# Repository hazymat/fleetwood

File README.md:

# fleetwood
Home Automation Room Controller

*** NOTE: Support for this project is not possible, however collaborators are warmly encouraged to contact me! ***

Project consists of:
- Arduino Sketch intended for Arduino Mega 2560
- Eagle files for 4 PC boards

1/ Sketch and Eagle schematics and board layouts are shared for information only.
2/ This project does not yet include an official BOM.

   Copyright 2015 Mat Smith

   Licensed under the Apache License, Version 2.0 (the "License");
   you may not use this file except in compliance with the License.
   You may obtain a copy of the License at

       http://www.apache.org/licenses/LICENSE-2.0

   Unless required by applicable law or agreed to in writing, software
   distributed under the License is distributed on an "AS IS" BASIS,
   WITHOUT WARRANTIES OR CONDITIONS OF ANY KIND, either express or implied.
   See the License for the specific language governing permissions and
   limitations under the License.

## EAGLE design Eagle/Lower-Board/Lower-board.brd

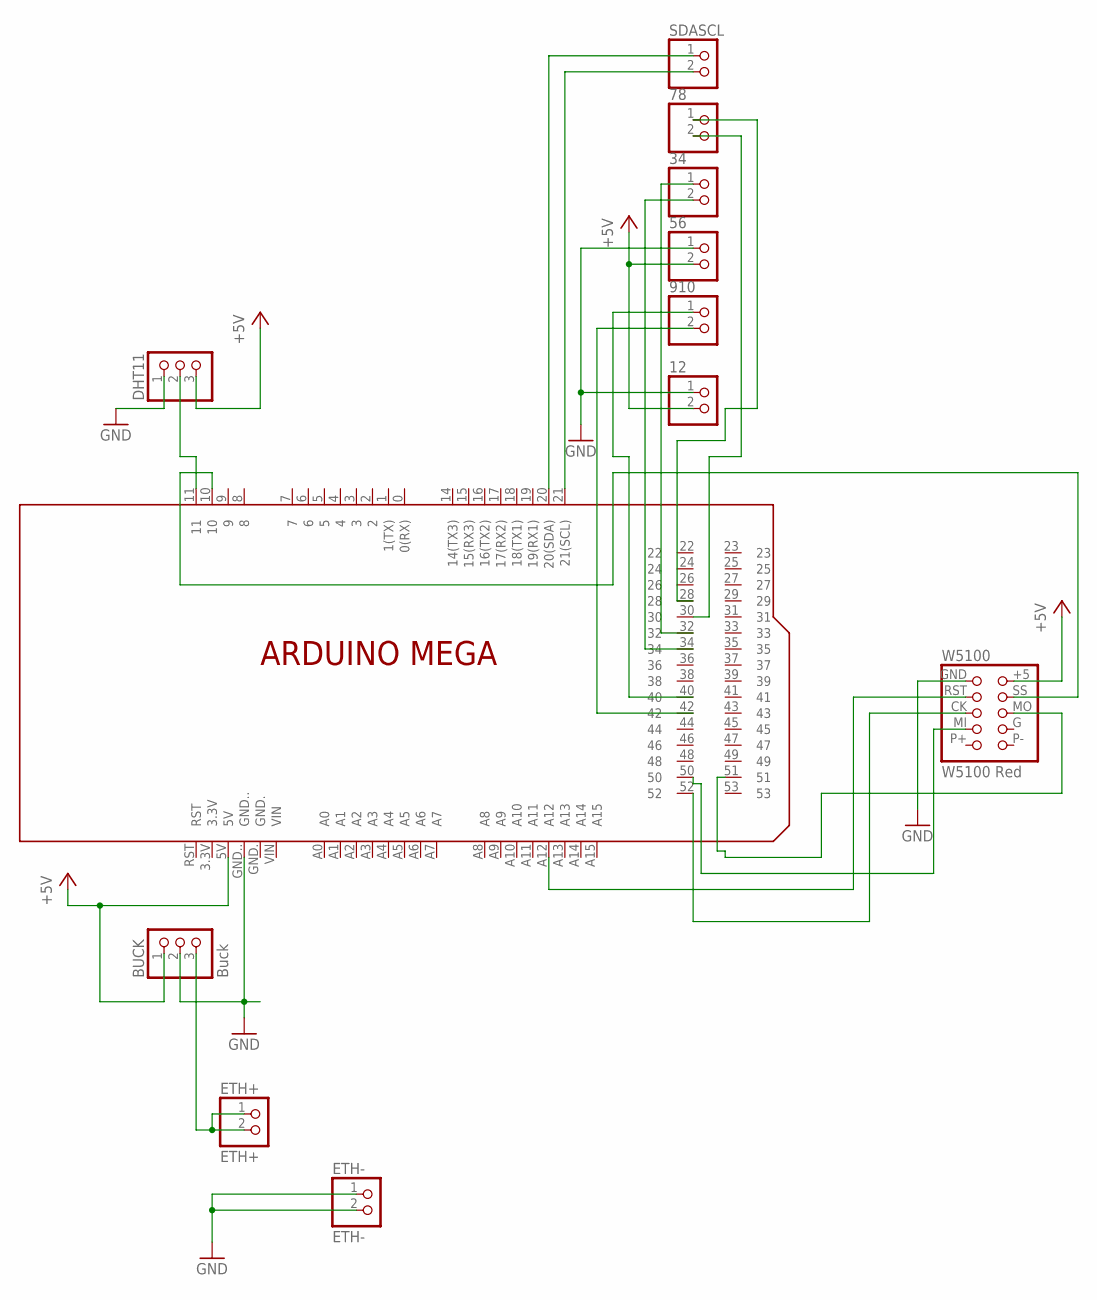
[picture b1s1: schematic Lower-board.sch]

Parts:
12, 34, 56, 78, 910: PINHD-1X2; 1X02
BUCK: Buck; 1X03
DHT11: PINHD-1X3; 1X03
ETH+: ETH+; 1X02
ETH-: ETH-; 1X02
SDASCL: PINHD-1X2; 1X02
U$1: ARDUINO_MEGA_1
W5100: W5100 Red; W5100-RED

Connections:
+5V: 12.2, 56.2, BUCK.1, DHT11.3, U$1.5V, W5100.+5
GND: 12.1, 56.1, BUCK.2, DHT11.1, ETH-.1, ETH-.2, U$1.GND.., W5100.GND
unnamed: BUCK.3, ETH+.1, ETH+.2
unnamed: SDASCL.2, U$1.21 (21(SCL))
unnamed: SDASCL.1, U$1.20 (20(SDA))
unnamed: DHT11.2, U$1.11
unnamed: 910.2, U$1.42
unnamed: 910.1, U$1.40
unnamed: 34.2, U$1.34
unnamed: 34.1, U$1.32
unnamed: 78.1, U$1.28
unnamed: 78.2, U$1.30
unnamed: U$1.52, W5100.CK
unnamed: U$1.50, W5100.MI
unnamed: U$1.A12, W5100.RST
unnamed: U$1.10, W5100.SS
unnamed: U$1.51, W5100.MO

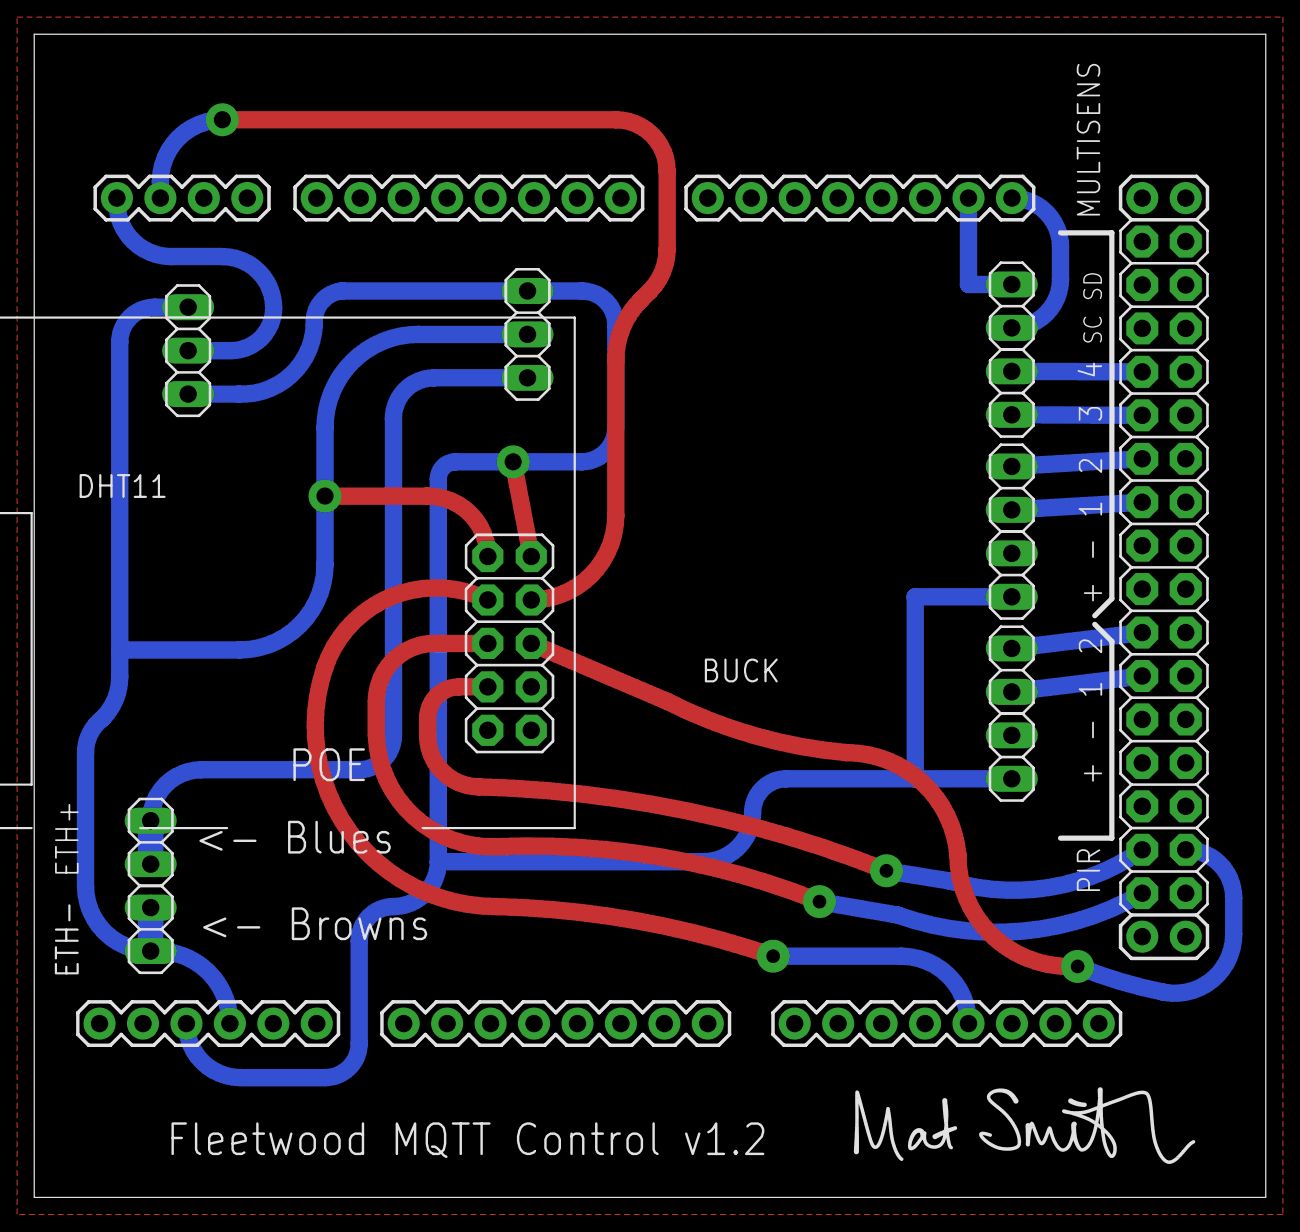
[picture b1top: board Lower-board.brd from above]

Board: 2 copper layers, 72.0 x 68.0 mm, 12 parts (0 on the bottom side), 17 nets.

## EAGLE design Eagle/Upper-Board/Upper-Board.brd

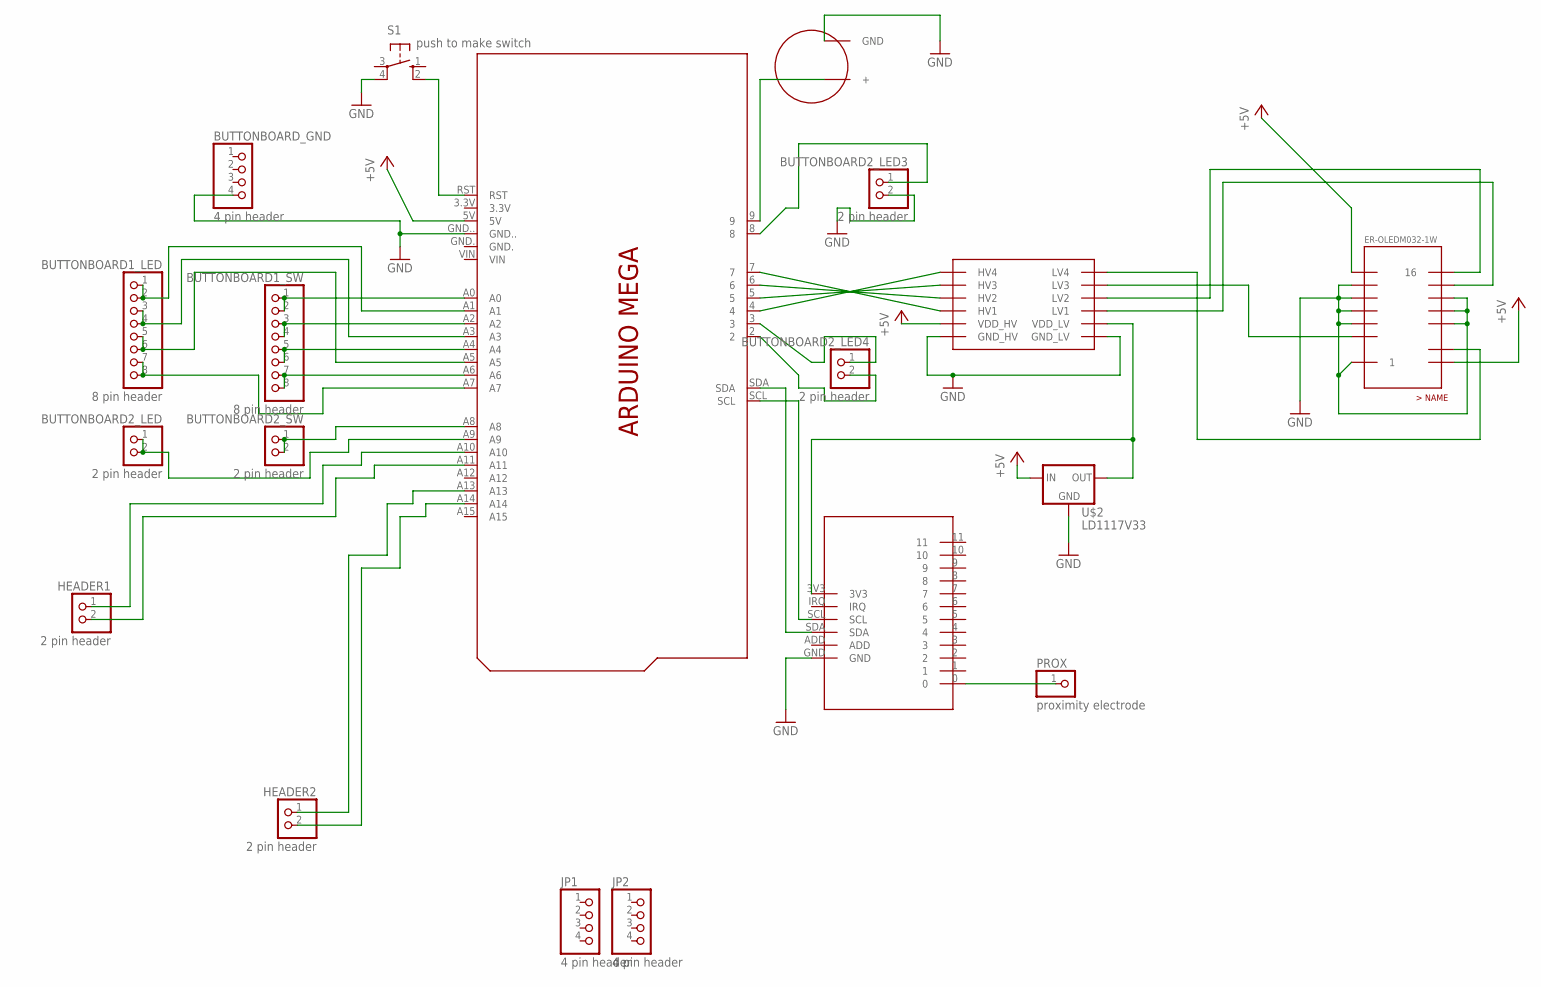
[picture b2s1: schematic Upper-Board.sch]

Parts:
BUTTONBOARD1_LED, BUTTONBOARD1_SW: 8 pin header; 1X08
BUTTONBOARD2_LED, BUTTONBOARD2_LED3, BUTTONBOARD2_LED4, BUTTONBOARD2_SW: 2 pin header; 1X02
BUTTONBOARD_GND: 4 pin header; 1X04
HEADER1, HEADER2: 2 pin header; 1X02
JP1, JP2: 4 pin header; 1X04
PROX: proximity electrode; 1X01
S1: push to make switch; B3F-10XX
U$1: ARDUINO_MEGA_2
U$2: LD1117V33
U$3: ER-OLED-M032-1W
U$4: BI_DIRECTIONAL_LEVEL_CONV
U$5: MPR121_BREAKOUT
U$6: BUZZER

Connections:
+5V: U$1.5V, U$2.IN, U$3.2, U$3.15, U$4.VDD_HV
GND: BUTTONBOARD2_LED3.2, BUTTONBOARD_GND.4, S1.4 (P1), U$1.GND.., U$2.GND, U$3.1, U$3.7, U$3.8, U$3.9, U$3.10, U$3.11, U$3.12, U$3.13, U$4.GND_HV, U$4.GND_LV, U$5.GND, U$6.GND
unnamed: BUTTONBOARD1_SW.1, BUTTONBOARD1_SW.2, U$1.A0
unnamed: BUTTONBOARD1_SW.3, BUTTONBOARD1_SW.4, U$1.A2
unnamed: BUTTONBOARD1_SW.5, BUTTONBOARD1_SW.6, U$1.A4
unnamed: BUTTONBOARD1_SW.7, BUTTONBOARD1_SW.8, U$1.A6
unnamed: BUTTONBOARD2_SW.1, BUTTONBOARD2_SW.2, U$1.A8
unnamed: BUTTONBOARD1_LED.1, BUTTONBOARD1_LED.2, U$1.A1
unnamed: U$1.SDA, U$5.SDA
unnamed: BUTTONBOARD1_LED.3, BUTTONBOARD1_LED.4, U$1.A3
unnamed: BUTTONBOARD1_LED.5, BUTTONBOARD1_LED.6, U$1.A5
unnamed: BUTTONBOARD1_LED.7, BUTTONBOARD1_LED.8, U$1.A7
unnamed: S1.2 (S1), U$1.RST
unnamed: BUTTONBOARD2_LED.1, BUTTONBOARD2_LED.2, U$1.A9
unnamed: U$1.SCL, U$5.SCL
unnamed: PROX.1, U$5.0
unnamed: U$1.9, U$6.+
unnamed: BUTTONBOARD2_LED3.1, U$1.8
unnamed: BUTTONBOARD2_LED4.1, U$1.3
unnamed: BUTTONBOARD2_LED4.2, U$1.2
unnamed: U$1.4, U$4.HV4
unnamed: U$1.5, U$4.HV3
unnamed: U$1.6, U$4.HV2
unnamed: U$1.7, U$4.HV1
unnamed: U$2.OUT, U$4.VDD_LV, U$5.3V3
unnamed: U$3.14, U$4.LV1
unnamed: U$3.16, U$4.LV2
unnamed: U$3.5, U$4.LV3
unnamed: U$3.4, U$4.LV4
unnamed: HEADER2.1, U$1.A13
unnamed: HEADER2.2, U$1.A14
unnamed: HEADER1.1, U$1.A10
unnamed: HEADER1.2, U$1.A11

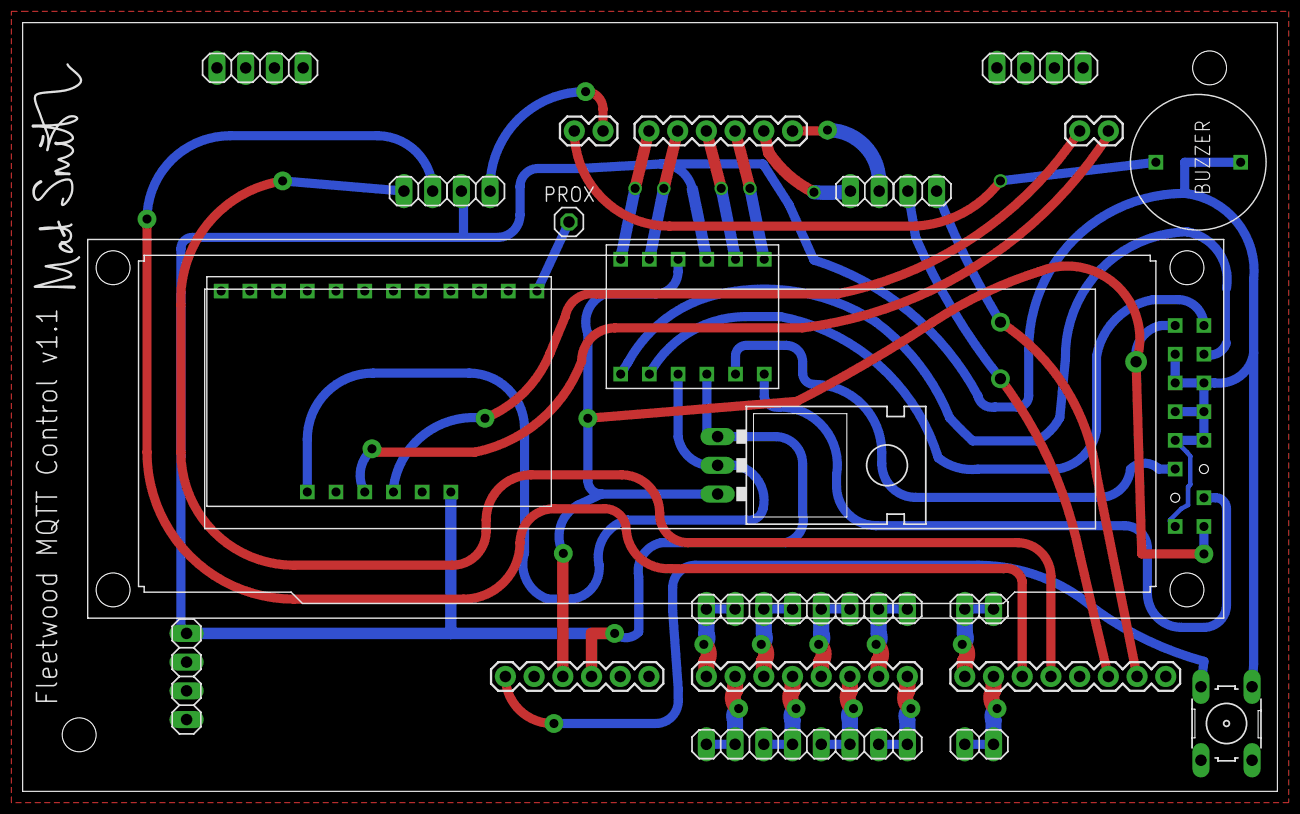
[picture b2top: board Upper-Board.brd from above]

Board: 2 copper layers, 111.0 x 68.0 mm, 19 parts (0 on the bottom side), 33 nets.

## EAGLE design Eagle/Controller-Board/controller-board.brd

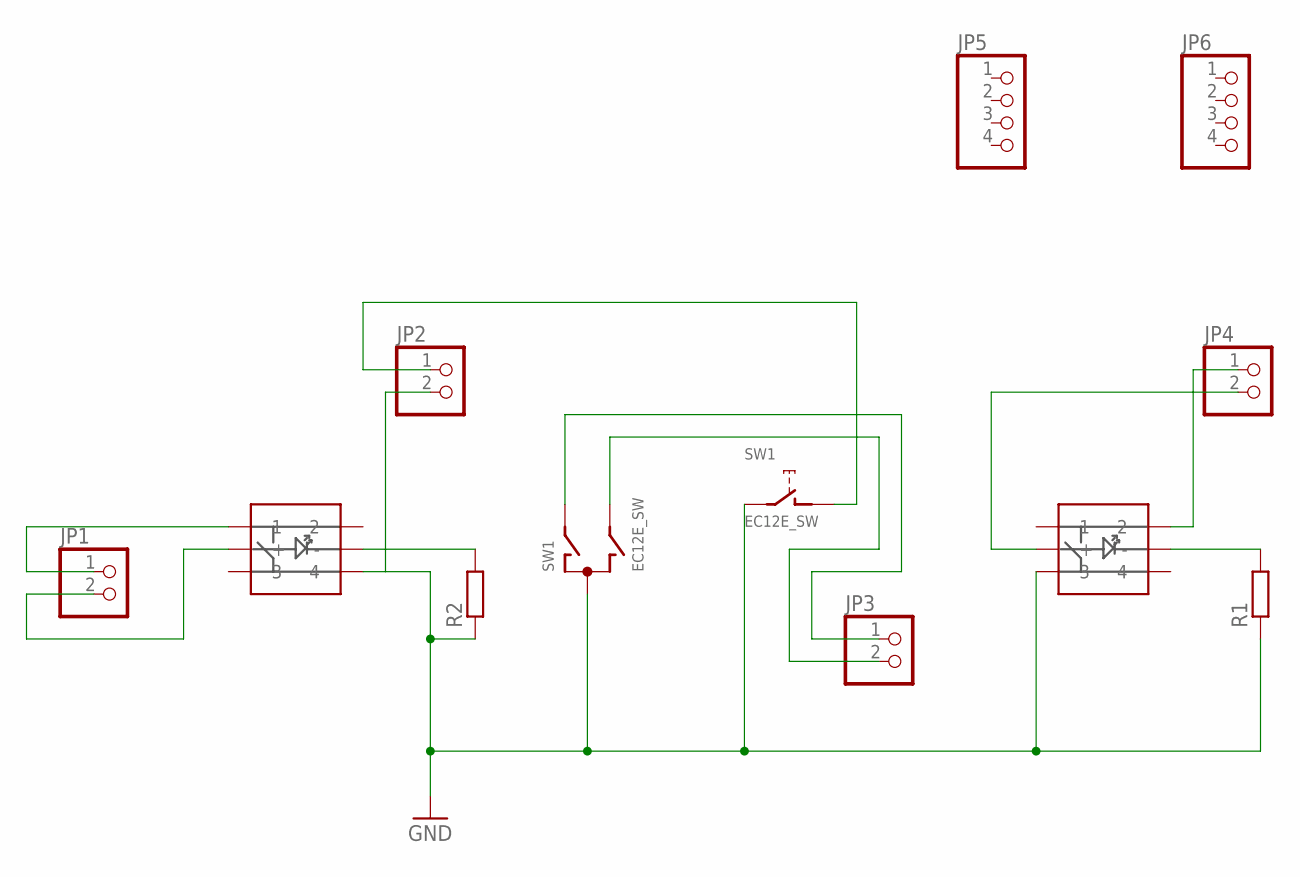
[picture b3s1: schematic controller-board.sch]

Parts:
BTN_MODE: PB614
BTN_OFF: PB614
JP1, JP2, JP3, JP4: PINHD-1X2; 1X02
JP5, JP6: PINHD-1X4; 1X04
R1, R2: R-EU_R1206; R1206
SW1: EC12E_SW; ALPS_EC12E_SW

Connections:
GND: BTN_MODE.4, BTN_OFF.3, JP2.2, R1.1, R2.1, SW1.C, SW1.E (2)
LED_MODE: BTN_MODE.L+ (+), JP1.2
unnamed: BTN_MODE.L- (-), R2.2
unnamed: BTN_OFF.L- (-), R1.2
unnamed: JP2.1, SW1.D (1)
unnamed: JP3.2, SW1.B
unnamed: JP3.1, SW1.A
unnamed: BTN_OFF.L+ (+), JP4.2
unnamed: BTN_OFF.2, JP4.1
SW_MODE: BTN_MODE.1, JP1.1

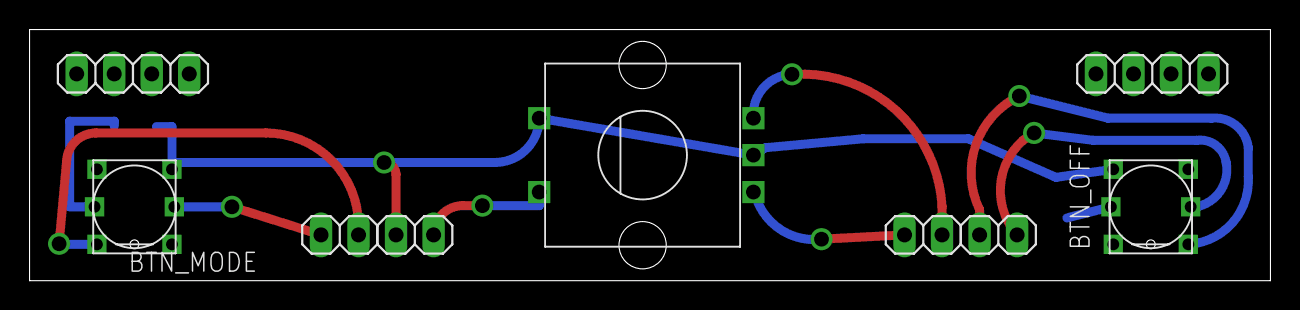
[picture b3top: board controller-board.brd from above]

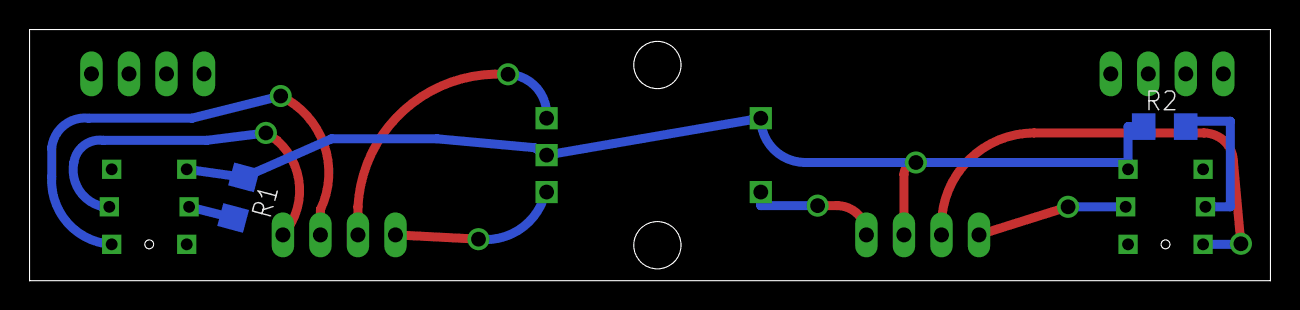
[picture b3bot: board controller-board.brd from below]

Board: 2 copper layers, 84.0 x 17.0 mm, 11 parts (2 on the bottom side), 10 nets.

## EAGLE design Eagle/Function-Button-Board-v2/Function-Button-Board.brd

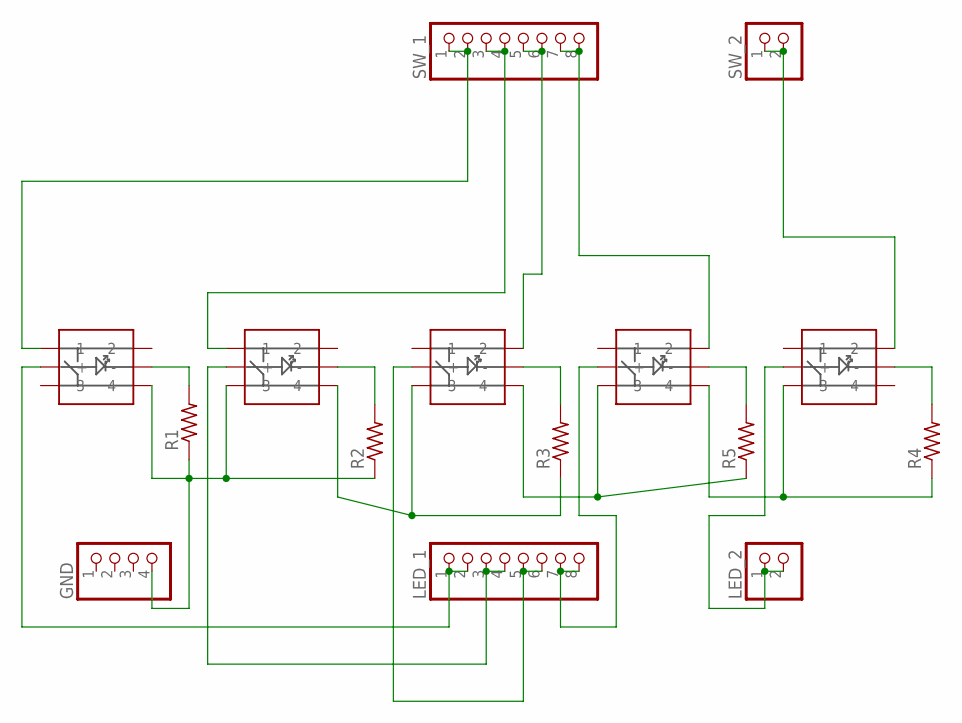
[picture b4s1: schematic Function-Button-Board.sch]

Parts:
FN_1, FN_2, FN_3, FN_4, FN_5: PB614
GND: PINHD-1X4; 1X04
LED_1: PINHD-1X8; 1X08
LED_2: PINHD-1X2; 1X02
R1, R2, R3, R4, R5: R-US_R1206; R1206
SW_1: PINHD-1X8; 1X08
SW_2: PINHD-1X2; 1X02

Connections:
unnamed: FN_1.L+ (+), LED_1.1, LED_1.2
unnamed: FN_1.L- (-), R1.2
unnamed: FN_1.1, SW_1.1, SW_1.2
unnamed: FN_3.L+ (+), LED_1.5, LED_1.6
unnamed: FN_1.4, FN_2.3, GND.4, R1.1, R2.1
unnamed: FN_4.L+ (+), LED_1.7, LED_1.8
unnamed: FN_2.1, SW_1.3, SW_1.4
unnamed: FN_2.L+ (+), LED_1.3, LED_1.4
unnamed: FN_5.L+ (+), LED_2.1, LED_2.2
unnamed: FN_2.L- (-), R2.2
unnamed: FN_3.L- (-), R3.2
unnamed: FN_2.4, FN_3.3, R3.1
unnamed: FN_4.L- (-), R5.2
unnamed: FN_5.L- (-), R4.2
unnamed: FN_3.2, SW_1.5, SW_1.6
unnamed: FN_3.4, FN_4.3, R5.1
unnamed: FN_5.2, SW_2.1, SW_2.2
unnamed: FN_4.2, SW_1.7, SW_1.8
unnamed: FN_4.4, FN_5.3, R4.1

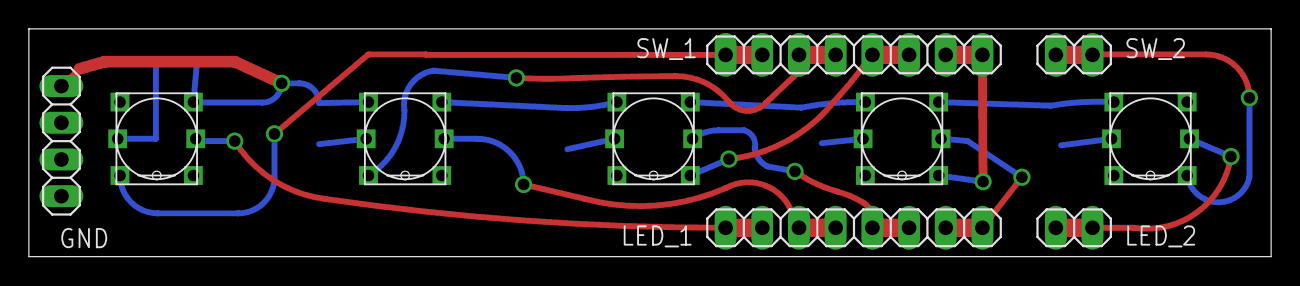
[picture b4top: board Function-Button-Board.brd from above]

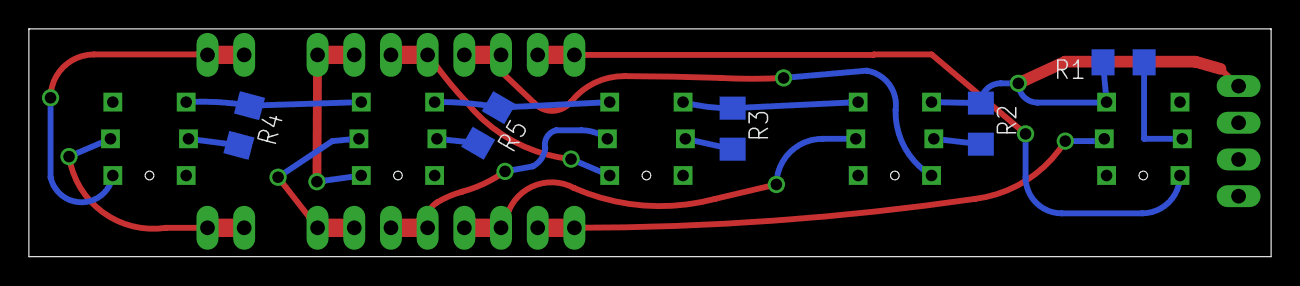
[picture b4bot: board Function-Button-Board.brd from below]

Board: 2 copper layers, 86.0 x 15.8 mm, 15 parts (5 on the bottom side), 19 nets.

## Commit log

2015-09-10 Addition of project code
2015-09-10 Licence
2015-09-10 remove unneeded tif
2015-09-10 test
2015-09-10 test removal
2015-09-10 Addition of board PDFs and tidy
2015-09-10 Addition of board layout PDFs
2015-09-21 Updating readme
2015-11-25 .\a42j5ze1.umn.txt
2016-01-11 - implemented heating mode with boiler status, current and set temp, and heating presets - started to move display text into u8g program memory: SRAM improvements - new weather mode and weather icon
2016-01-12 - 5 day weather forecast - further memory improvements - other minor imorovements
